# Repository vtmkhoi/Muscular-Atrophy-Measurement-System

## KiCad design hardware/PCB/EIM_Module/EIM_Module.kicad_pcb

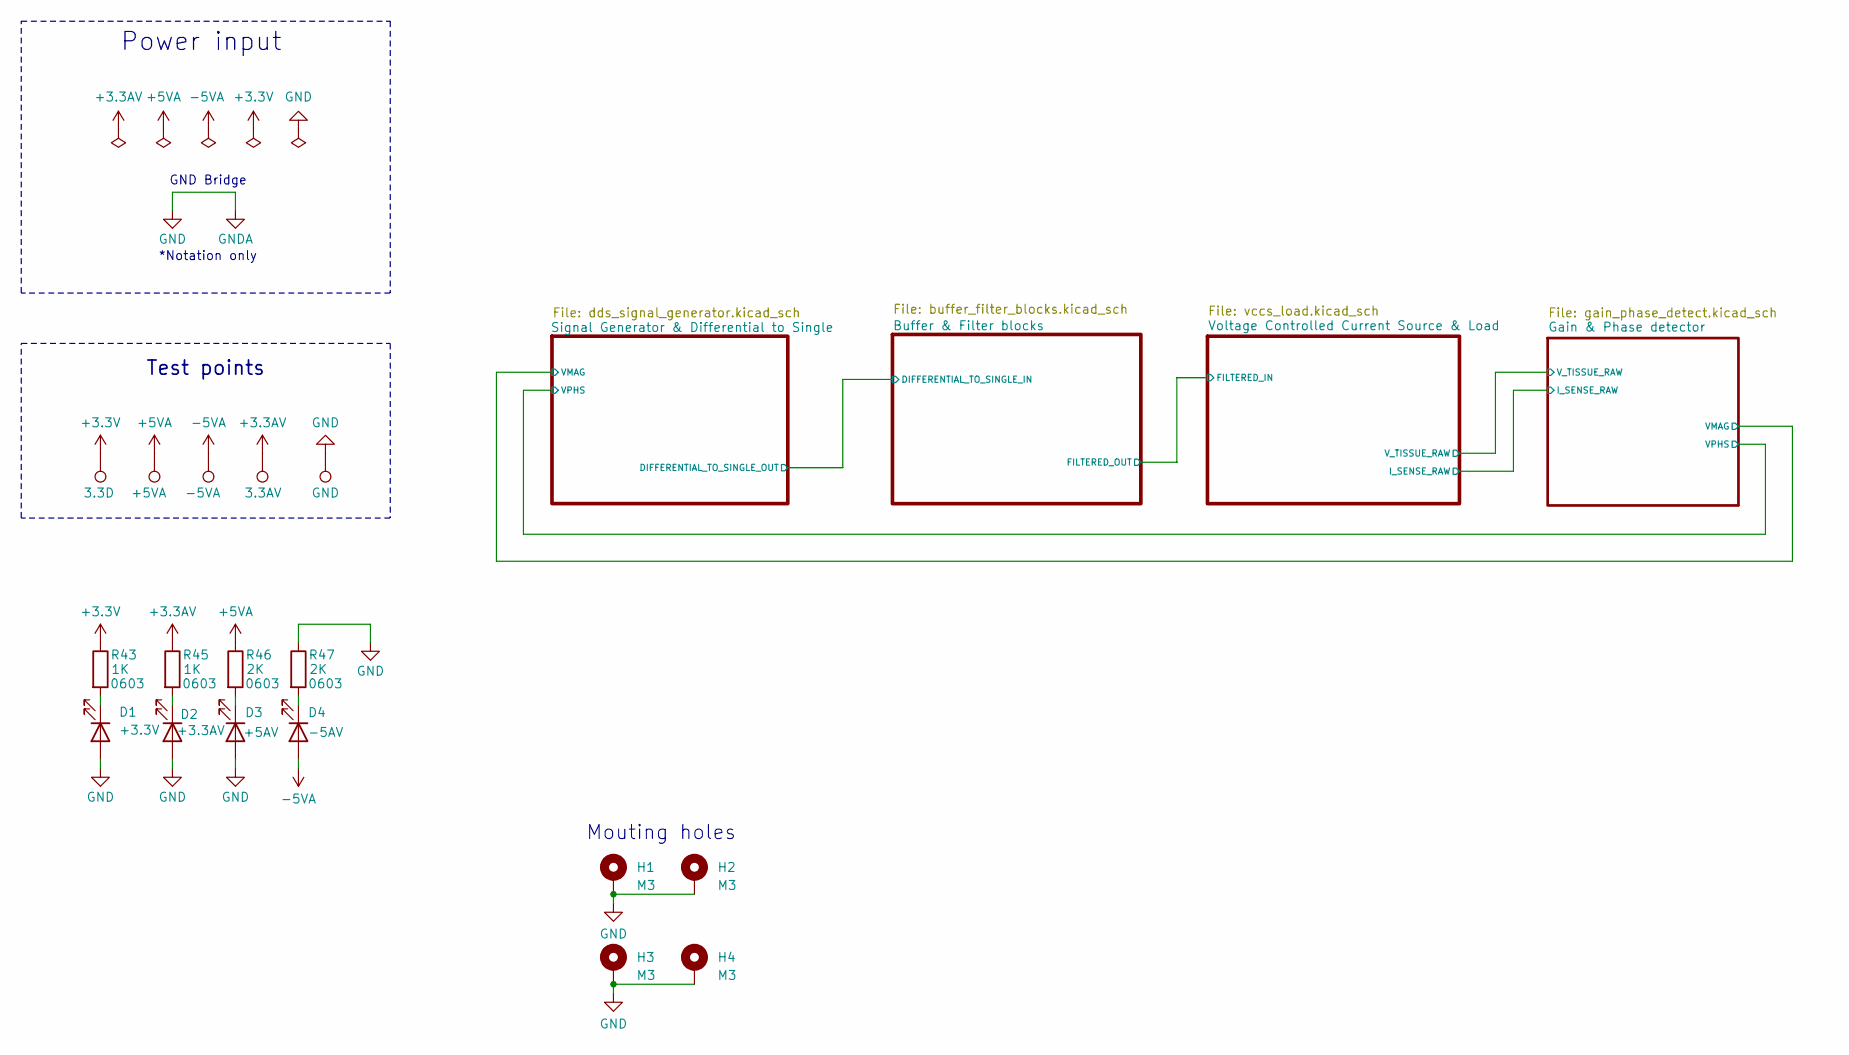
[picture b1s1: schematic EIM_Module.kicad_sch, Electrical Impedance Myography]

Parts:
D1: +3.3V; LED_0603_1608Metric
D2: +3.3AV; LED_0603_1608Metric
D3: +5AV; LED_0603_1608Metric
D4: -5AV; LED_0603_1608Metric
H1, H2, H3, H4: M3; MountingHole_3.2mm_M3_Pad_Via
R43, R45: 1K; R_0603_1608Metric
R46, R47: 2K; R_0603_1608Metric
TP11: 3.3D; TestPoint_Pad_D1.0mm
TP12: +5VA; TestPoint_Pad_D1.0mm
TP13: -5VA; TestPoint_Pad_D1.0mm
TP14: GND; TestPoint_Pad_D1.0mm
TP29: 3.3AV; TestPoint_Pad_D1.0mm

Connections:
+3.3AV: R45.1, TP29.1; also elsewhere on the board
+3.3V: R43.1, TP11.1; also elsewhere on the board
+5VA: R46.1, TP12.1; also elsewhere on the board
-5VA: D4.2 (A), TP13.1; also elsewhere on the board
GND: D1.2 (A), D2.2 (A), D3.2 (A), H1.1, H2.1, H3.1, H4.1, R47.1, TP14.1; also elsewhere on the board
unnamed: D1.1 (K), R43.2
unnamed: D2.1 (K), R45.2
unnamed: D3.1 (K), R46.2
unnamed: D4.1 (K), R47.2

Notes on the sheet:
Power input
GND Bridge
Test points
*Notation only
Mouting holes

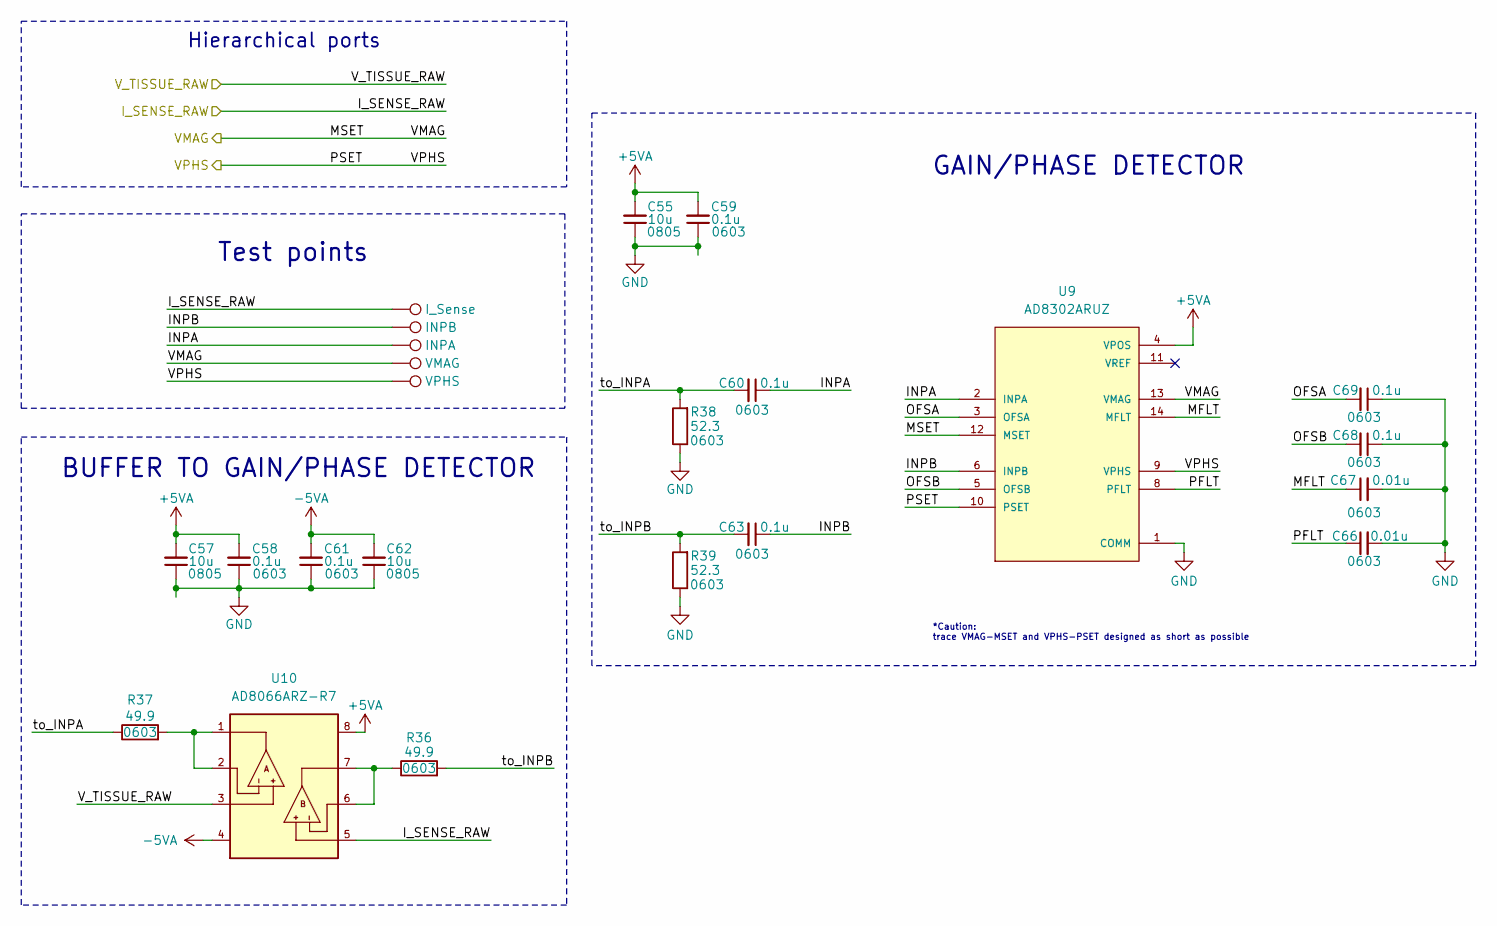
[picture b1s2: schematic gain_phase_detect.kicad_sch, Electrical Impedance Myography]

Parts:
C55, C57, C62: 10u; C_0805_2012Metric
C58, C59, C60, C61, C63, C68, C69: 0.1u; C_0603_1608Metric
C66, C67: 0.01u; C_0603_1608Metric
R36, R37: 49.9; R_0603_1608Metric
R38, R39: 52.3; R_0603_1608Metric
TP21: INPA; TestPoint_Pad_D1.0mm
TP27: I_Sense; TestPoint_Pad_D1.0mm
TP28: INPB; TestPoint_Pad_D1.0mm
TP30: VMAG; TestPoint_Pad_D1.0mm
TP31: VPHS; TestPoint_Pad_D1.0mm
U9: AD8302ARUZ; SOP65P640X120-14N; PARTREV B
U10: AD8066ARZ-R7; SOIC127P600X175-8N

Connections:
+5VA: C55.2, C57.2, C58.2, C59.2, U9.4 (VPOS), U10.8; also elsewhere on the board
-5VA: C61.2, C62.2, U10.4; also elsewhere on the board
/Gain & Phase detector/INPA: C60.1, TP21.1, U9.2 (INPA)
/Gain & Phase detector/INPB: C63.1, TP28.1, U9.6 (INPB)
/Gain & Phase detector/I_SENSE_RAW: TP27.1, U10.5; also elsewhere on the board
/Gain & Phase detector/MFLT: C67.1, U9.14 (MFLT)
/Gain & Phase detector/MSET: TP30.1, U9.12 (MSET), U9.13 (VMAG); also elsewhere on the board
/Gain & Phase detector/OFSA: C69.2, U9.3 (OFSA)
/Gain & Phase detector/OFSB: C68.2, U9.5 (OFSB)
/Gain & Phase detector/PFLT: C66.1, U9.8 (PFLT)
/Gain & Phase detector/PSET: TP31.1, U9.9 (VPHS), U9.10 (PSET); also elsewhere on the board
/Gain & Phase detector/V_TISSUE_RAW: U10.3; also elsewhere on the board
/Gain & Phase detector/to_INPA: C60.2, R37.1, R38.2
/Gain & Phase detector/to_INPB: C63.2, R36.2, R39.2
GND: C55.1, C57.1, C58.1, C59.1, C61.1, C62.1, C66.2, C67.2, C68.1, C69.1, R38.1, R39.1, U9.1 (COMM), U9.7 (COMM); also elsewhere on the board
unnamed: R36.1, U10.6, U10.7
unnamed: R37.2, U10.1, U10.2

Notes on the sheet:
Test points
Hierarchical ports
GAIN/PHASE DETECTOR
BUFFER TO GAIN/PHASE DETECTOR
*Caution: trace VMAG-MSET and VPHS-PSET designed as short as possible

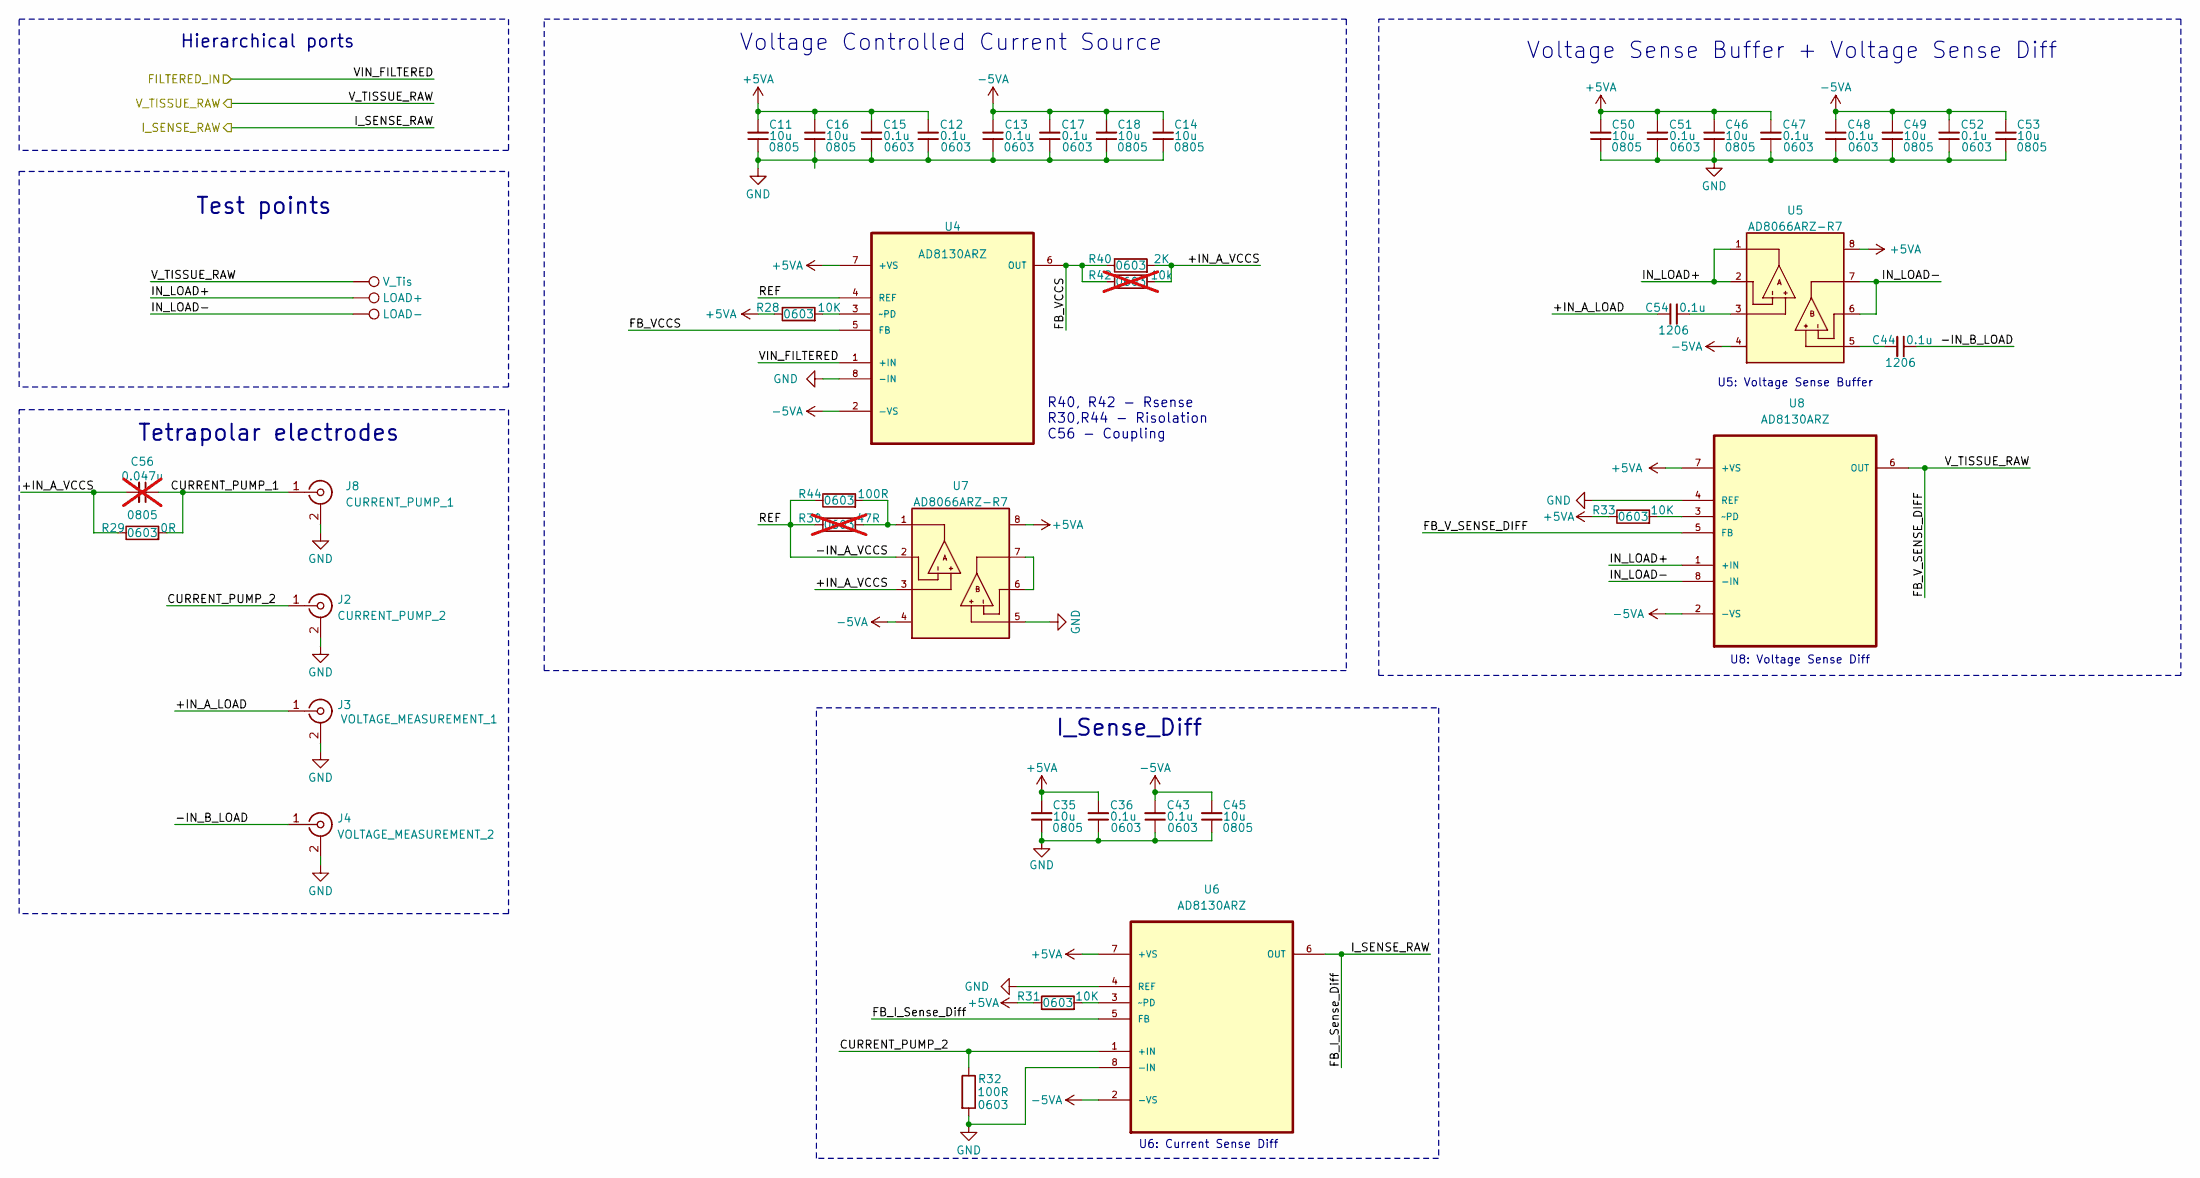
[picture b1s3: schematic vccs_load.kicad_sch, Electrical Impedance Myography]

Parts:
C11, C14, C16, C18, C35, C45, C46, C49, C50, C53: 10u; C_0805_2012Metric
C12, C13, C15, C17, C36, C43, C47, C48, C51, C52: 0.1u; C_0603_1608Metric
C44, C54: 0.1u; C_1206_3216Metric
C56: 0.047u; C_0805_2012Metric; not fitted
J2: CURRENT_PUMP_2; SMA_Molex_73251-2200_Horizontal
J3: VOLTAGE_MEASUREMENT_1; SMA_Molex_73251-2200_Horizontal
J4: VOLTAGE_MEASUREMENT_2; SMA_Molex_73251-2200_Horizontal
J8: CURRENT_PUMP_1; SMA_Molex_73251-2200_Horizontal
R28, R31, R33: 10K; R_0603_1608Metric
R29: 0R; R_0603_1608Metric
R30: 47R; R_0603_1608Metric; not fitted
R32, R44: 100R; R_0603_1608Metric
R40: 2K; R_0603_1608Metric
R42: 10k; R_0603_1608Metric; not fitted
TP17: V_Tis; TestPoint_Pad_D1.0mm
TP19: LOAD+; TestPoint_Pad_D1.0mm
TP20: LOAD-; TestPoint_Pad_D1.0mm
U4, U6, U8: AD8130ARZ; SOIC127P600X175-8N; MPN AD8130ARZ
U5, U7: AD8066ARZ-R7; SOIC127P600X175-8N

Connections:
+5VA: C11.2, C12.2, C15.2, C16.2, C35.2, C36.2, C46.2, C47.2, C50.2, C51.2, R28.1, R31.1, R33.1, U4.7 (+VS), U5.8, U6.7 (+VS), U7.8, U8.7 (+VS); also elsewhere on the board
-5VA: C13.2, C14.2, C17.2, C18.2, C43.2, C45.2, C48.2, C49.2, C52.2, C53.2, U4.2 (-VS), U5.4, U6.2 (-VS), U7.4, U8.2 (-VS); also elsewhere on the board
/Buffer & Filter blocks/VOUT_FILTERED: U4.1 (+IN); also elsewhere on the board
/Gain & Phase detector/I_SENSE_RAW: U6.5 (FB), U6.6 (OUT); also elsewhere on the board
/Gain & Phase detector/V_TISSUE_RAW: TP17.1, U8.5 (FB), U8.6 (OUT); also elsewhere on the board
/Voltage Controlled Current Source & Load/+IN_A_LOAD: C54.2, J3.1 (In)
/Voltage Controlled Current Source & Load/+IN_A_VCCS: C56.2, R29.1, R40.2, R42.2, U7.3
/Voltage Controlled Current Source & Load/-IN_A_VCCS: R30.1, R44.1, U4.4 (REF), U7.2
/Voltage Controlled Current Source & Load/-IN_B_LOAD: C44.1, J4.1 (In)
/Voltage Controlled Current Source & Load/CURRENT_PUMP_1: C56.1, J8.1 (In), R29.2
/Voltage Controlled Current Source & Load/CURRENT_PUMP_2: J2.1 (In), R32.1, U6.1 (+IN)
/Voltage Controlled Current Source & Load/FB_VCCS: R40.1, R42.1, U4.5 (FB), U4.6 (OUT)
/Voltage Controlled Current Source & Load/IN_LOAD+: TP19.1, U5.1, U5.2, U8.1 (+IN)
/Voltage Controlled Current Source & Load/IN_LOAD-: TP20.1, U5.6, U5.7, U8.8 (-IN)
GND: C11.1, C12.1, C13.1, C14.1, C15.1, C16.1, C17.1, C18.1, C35.1, C36.1, C43.1, C45.1, C46.1, C47.1, C48.1, C49.1, C50.1, C51.1, C52.1, C53.1, J2.2 (Ext), J3.2 (Ext), J4.2 (Ext), J8.2 (Ext), R32.2, U4.8 (-IN), U6.4 (REF), U6.8 (-IN), U7.5, U8.4 (REF); also elsewhere on the board
unnamed: C44.2, U5.5
unnamed: C54.1, U5.3
unnamed: R30.2, R44.2, U7.1
unnamed: R28.2, U4.3 (~PD)
unnamed: R31.2, U6.3 (~PD)
unnamed: U7.6, U7.7
unnamed: R33.2, U8.3 (~PD)

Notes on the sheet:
Test points
Voltage Controlled Current Source
R40, R42 - Rsense R30,R44 - Risolation C56 - Coupling
U8: Voltage Sense Diff
Voltage Sense Buffer + Voltage Sense Diff
Tetrapolar electrodes
U5: Voltage Sense Buffer
Hierarchical ports
I_Sense_Diff
U6: Current Sense Diff

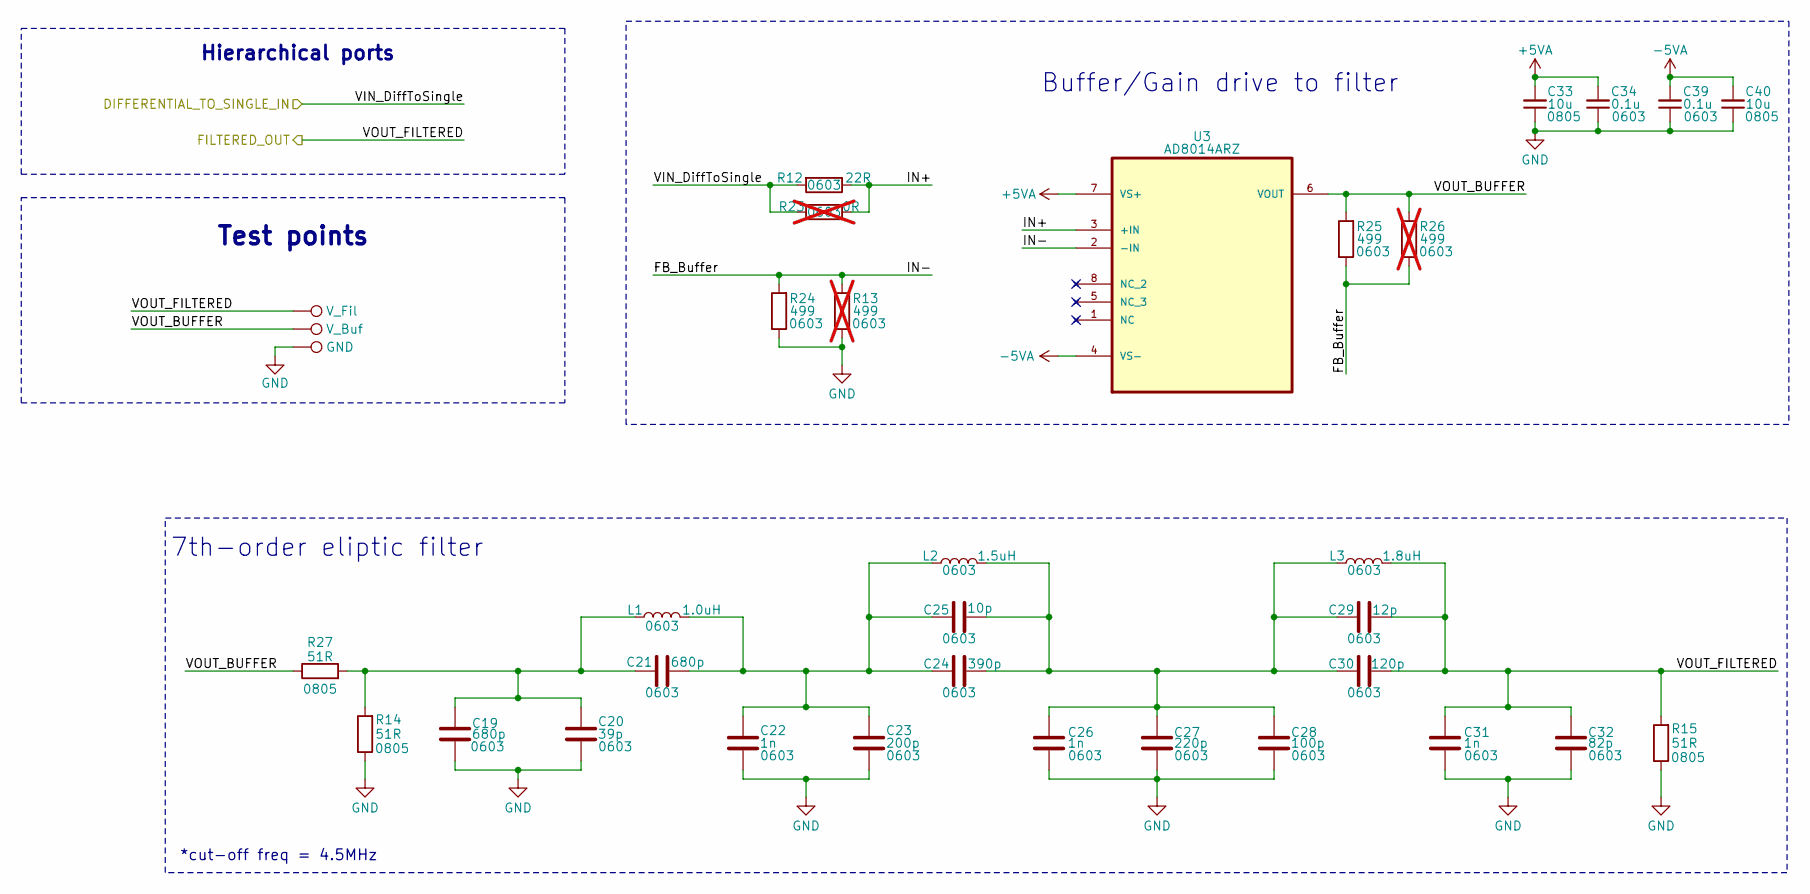
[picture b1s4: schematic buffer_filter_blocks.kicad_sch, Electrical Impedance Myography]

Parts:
C19, C21: 680p; C_0603_1608Metric
C20: 39p; C_0603_1608Metric
C22, C26, C31: 1n; C_0603_1608Metric
C23: 200p; C_0603_1608Metric
C24: 390p; C_0603_1608Metric
C25: 10p; C_0603_1608Metric
C27: 220p; C_0603_1608Metric
C28: 100p; C_0603_1608Metric
C29: 12p; C_0603_1608Metric
C30: 120p; C_0603_1608Metric
C32: 82p; C_0603_1608Metric
C33, C40: 10u; C_0805_2012Metric
C34, C39: 0.1u; C_0603_1608Metric
L1: 1.0uH; L_0603_1608Metric
L2: 1.5uH; L_0603_1608Metric
L3: 1.8uH; L_0603_1608Metric
R12: 22R; R_0603_1608Metric
R13, R26: 499; R_0603_1608Metric; not fitted
R14, R15, R27: 51R; R_0805_2012Metric
R23: 0R; R_0603_1608Metric; not fitted
R24, R25: 499; R_0603_1608Metric
TP22: V_Fil; TestPoint_Pad_D1.0mm
TP23: V_Buf; TestPoint_Pad_D1.0mm
TP25: GND; TestPoint_Pad_D1.0mm
U3: AD8014ARZ; SOIC127P600X175-8N; MPN AD8014ARZ

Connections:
+5VA: C33.2, C34.2, U3.7 (VS+); also elsewhere on the board
-5VA: C39.2, C40.2, U3.4 (VS-); also elsewhere on the board
/Buffer & Filter blocks/FB_Buffer: R13.2, R24.2, R25.1, R26.1, U3.2 (-IN)
/Buffer & Filter blocks/IN+: R12.1, R23.1, U3.3 (+IN)
/Buffer & Filter blocks/VIN_DiffToSingle: R12.2, R23.2; also elsewhere on the board
/Buffer & Filter blocks/VOUT_BUFFER: R25.2, R26.2, R27.1, TP23.1, U3.6 (VOUT)
/Buffer & Filter blocks/VOUT_FILTERED: C29.1, C30.1, C31.2, C32.2, L3.2, R15.2, TP22.1; also elsewhere on the board
GND: C19.1, C20.1, C22.1, C23.1, C26.1, C27.1, C28.1, C31.1, C32.1, C33.1, C34.1, C39.1, C40.1, R13.1, R14.1, R15.1, R24.1, TP25.1; also elsewhere on the board
unnamed: C19.2, C20.2, C21.2, L1.1, R14.2, R27.2
unnamed: C21.1, C22.2, C23.2, C24.2, C25.2, L1.2, L2.1
unnamed: C24.1, C25.1, C26.2, C27.2, C28.2, C29.2, C30.2, L2.2, L3.1

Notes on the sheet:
Hierarchical ports
*cut-off freq = 4.5MHz
7th-order eliptic filter
Test points
Buffer/Gain drive to filter

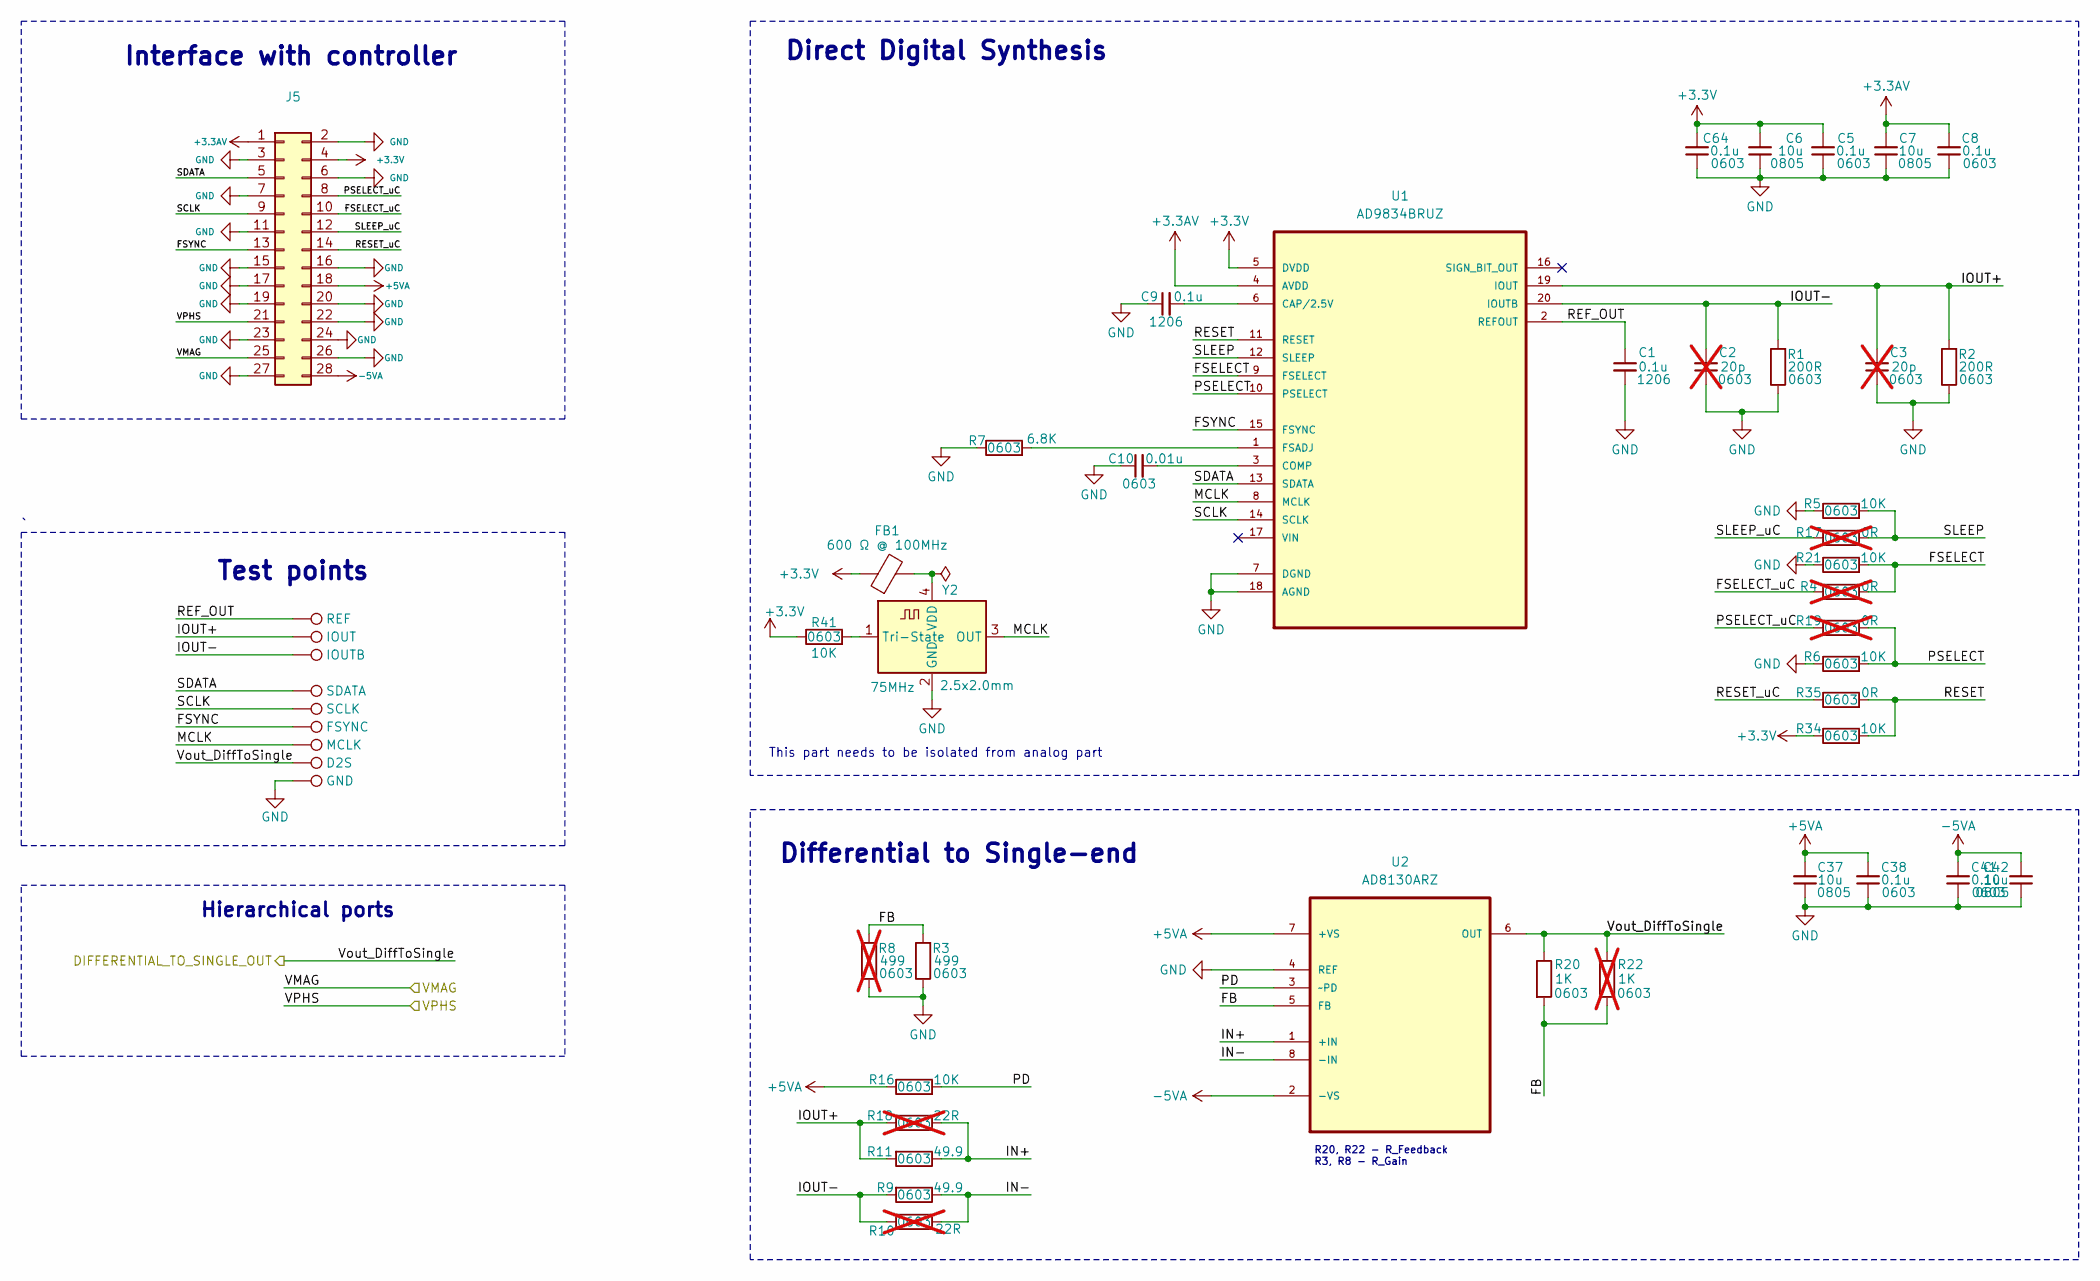
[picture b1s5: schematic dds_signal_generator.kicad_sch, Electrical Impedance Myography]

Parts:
C1, C9: 0.1u; C_1206_3216Metric
C2, C3: 20p; C_0603_1608Metric; not fitted
C5, C8, C38, C41, C64: 0.1u; C_0603_1608Metric
C6, C7, C37, C42: 10u; C_0805_2012Metric
C10: 0.01u; C_0603_1608Metric
FB1: 600 Ω @ 100MHz; L_0603_1608Metric
J5: Interface with controller; PinSocket_2x14_P2.00mm_Vertical
R1, R2: 200R; R_0603_1608Metric
R3: 499; R_0603_1608Metric
R4, R17, R19: 0R; R_0603_1608Metric; not fitted
R5, R6, R16, R21, R34, R41: 10K; R_0603_1608Metric
R7: 6.8K; R_0603_1608Metric
R8: 499; R_0603_1608Metric; not fitted
R9, R11: 49.9; R_0603_1608Metric
R10, R18: 22R; R_0603_1608Metric; not fitted
R20: 1K; R_0603_1608Metric
R22: 1K; R_0603_1608Metric; not fitted
R35: 0R; R_0603_1608Metric
TP1: REF; TestPoint_Pad_D1.0mm
TP2: IOUT; TestPoint_Pad_D1.0mm
TP3: IOUTB; TestPoint_Pad_D1.0mm
TP5: SDATA; TestPoint_Pad_D1.0mm
TP6: SCLK; TestPoint_Pad_D1.0mm
TP7: FSYNC; TestPoint_Pad_D1.0mm
TP8: MCLK; TestPoint_Pad_D1.0mm
TP9: GND; TestPoint_Pad_D1.0mm
TP10: D2S; TestPoint_Pad_D1.0mm
U1: AD9834BRUZ; SOP65P640X120-20N; MPN AD9834BRUZ
U2: AD8130ARZ; SOIC127P600X175-8N; MPN AD8130ARZ
Y2: 75MHz; Oscillator_SMD_SeikoEpson_SG210-4Pin_2.5x2.0mm

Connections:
+3.3AV: C7.2, C8.2, J5.1, U1.4 (AVDD); also elsewhere on the board
+3.3V: C5.2, C6.2, C64.2, FB1.1, J5.4, R34.1, R41.1, U1.5 (DVDD); also elsewhere on the board
+5VA: C37.2, C38.2, J5.18, R16.1, U2.7 (+VS); also elsewhere on the board
-5VA: C41.2, C42.2, J5.28, U2.2 (-VS); also elsewhere on the board
/Buffer & Filter blocks/VIN_DiffToSingle: R20.1, R22.1, TP10.1, U2.6 (OUT); also elsewhere on the board
/Gain & Phase detector/MSET: J5.25; also elsewhere on the board
/Gain & Phase detector/PSET: J5.21; also elsewhere on the board
/Signal Generator & Differential to Single/FB: R3.2, R8.2, R20.2, R22.2, U2.5 (FB)
/Signal Generator & Differential to Single/FSELECT: R4.2, R21.2, U1.9 (FSELECT)
/Signal Generator & Differential to Single/FSELECT_uC: J5.10, R4.1
/Signal Generator & Differential to Single/FSYNC: J5.13, TP7.1, U1.15 (FSYNC)
/Signal Generator & Differential to Single/IN+: R11.1, R18.1, U2.1 (+IN)
/Signal Generator & Differential to Single/IN-: R9.1, R10.1, U2.8 (-IN)
/Signal Generator & Differential to Single/IOUT+: C3.2, R2.2, R11.2, R18.2, TP2.1, U1.19 (IOUT)
/Signal Generator & Differential to Single/IOUT-: C2.2, R1.2, R9.2, R10.2, TP3.1, U1.20 (IOUTB)
/Signal Generator & Differential to Single/MCLK: TP8.1, U1.8 (MCLK), Y2.3 (OUT)
/Signal Generator & Differential to Single/PD: R16.2, U2.3 (~PD)
/Signal Generator & Differential to Single/PSELECT: R6.2, R19.2, U1.10 (PSELECT)
/Signal Generator & Differential to Single/PSELECT_uC: J5.8, R19.1
/Signal Generator & Differential to Single/REF_OUT: C1.1, TP1.1, U1.2 (REFOUT)
/Signal Generator & Differential to Single/RESET: R34.2, R35.2, U1.11 (RESET)
/Signal Generator & Differential to Single/RESET_uC: J5.14, R35.1
/Signal Generator & Differential to Single/SCLK: J5.9, TP6.1, U1.14 (SCLK)
/Signal Generator & Differential to Single/SDATA: J5.5, TP5.1, U1.13 (SDATA)
/Signal Generator & Differential to Single/SLEEP: R5.2, R17.2, U1.12 (SLEEP)
/Signal Generator & Differential to Single/SLEEP_uC: J5.12, R17.1
GND: C1.2, C2.1, C3.1, C5.1, C6.1, C7.1, C8.1, C9.1, C10.1, C37.1, C38.1, C41.1, C42.1, C64.1, J5.2, J5.3, J5.6, J5.7, J5.11, J5.15, J5.16, J5.17, J5.19, J5.20, J5.22, J5.23, J5.24, J5.26, J5.27, R1.1, R2.1, R3.1, R5.1, R6.1, R7.1, R8.1, R21.1, TP9.1, U1.7 (DGND), U1.18 (AGND), U2.4 (REF), Y2.2 (GND); also elsewhere on the board
unnamed: C9.2, U1.6 (CAP/2.5V)
unnamed: C10.2, U1.3 (COMP)
unnamed: R7.2, U1.1 (FSADJ)
unnamed: R41.2, Y2.1 (Tri-State)
unnamed: FB1.2, Y2.4 (VDD)

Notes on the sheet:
This part needs to be isolated from analog part
Interface with controller
Direct Digital Synthesis
Differential to Single-end
R20, R22 - R_Feedback R3, R8 - R_Gain
Test points
Hierarchical ports

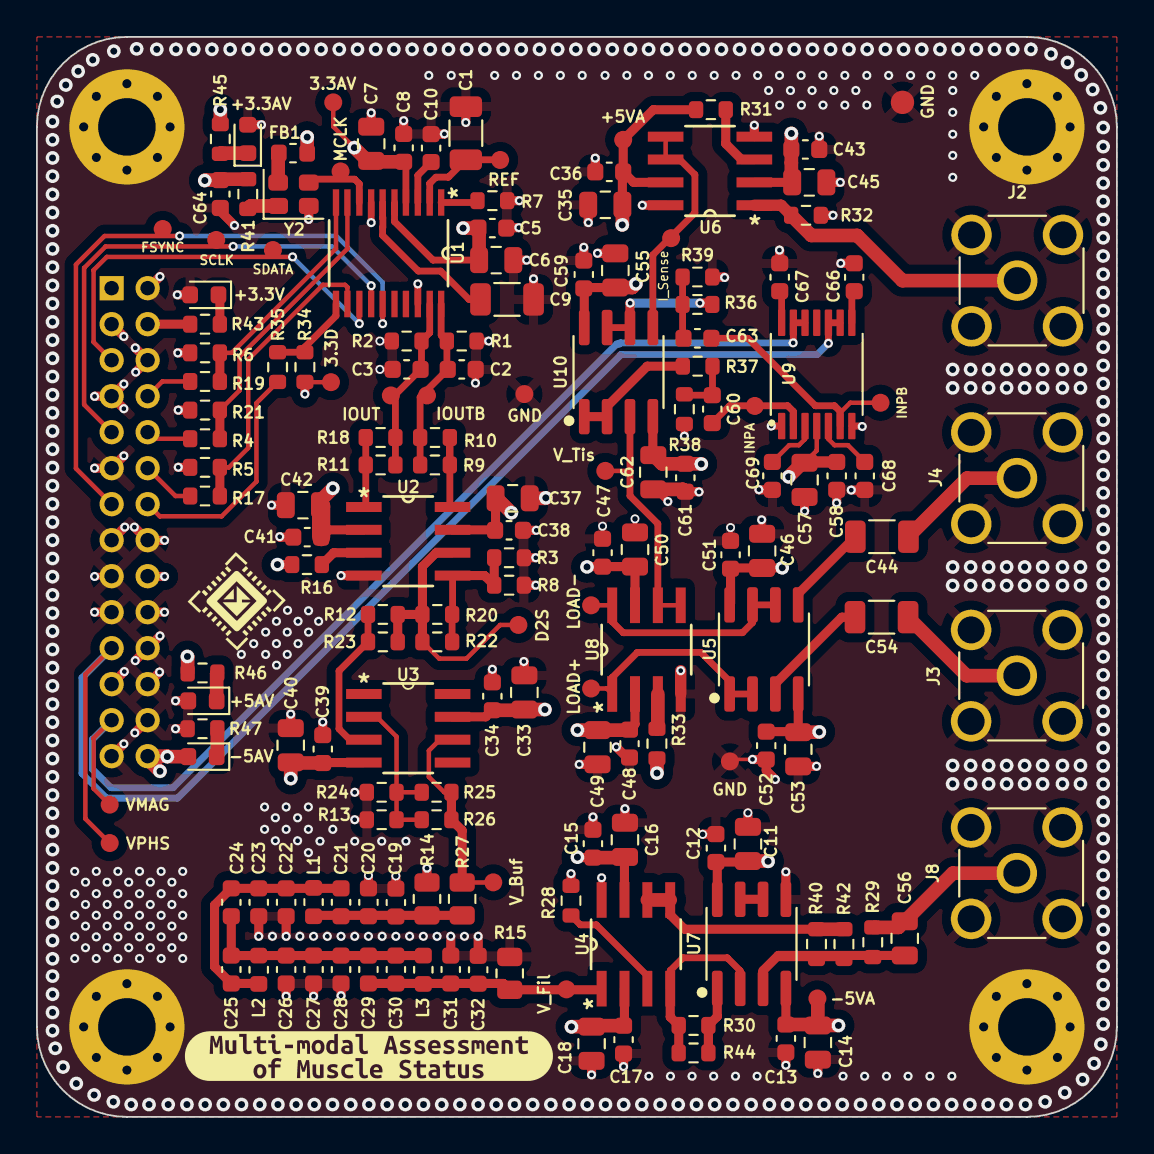
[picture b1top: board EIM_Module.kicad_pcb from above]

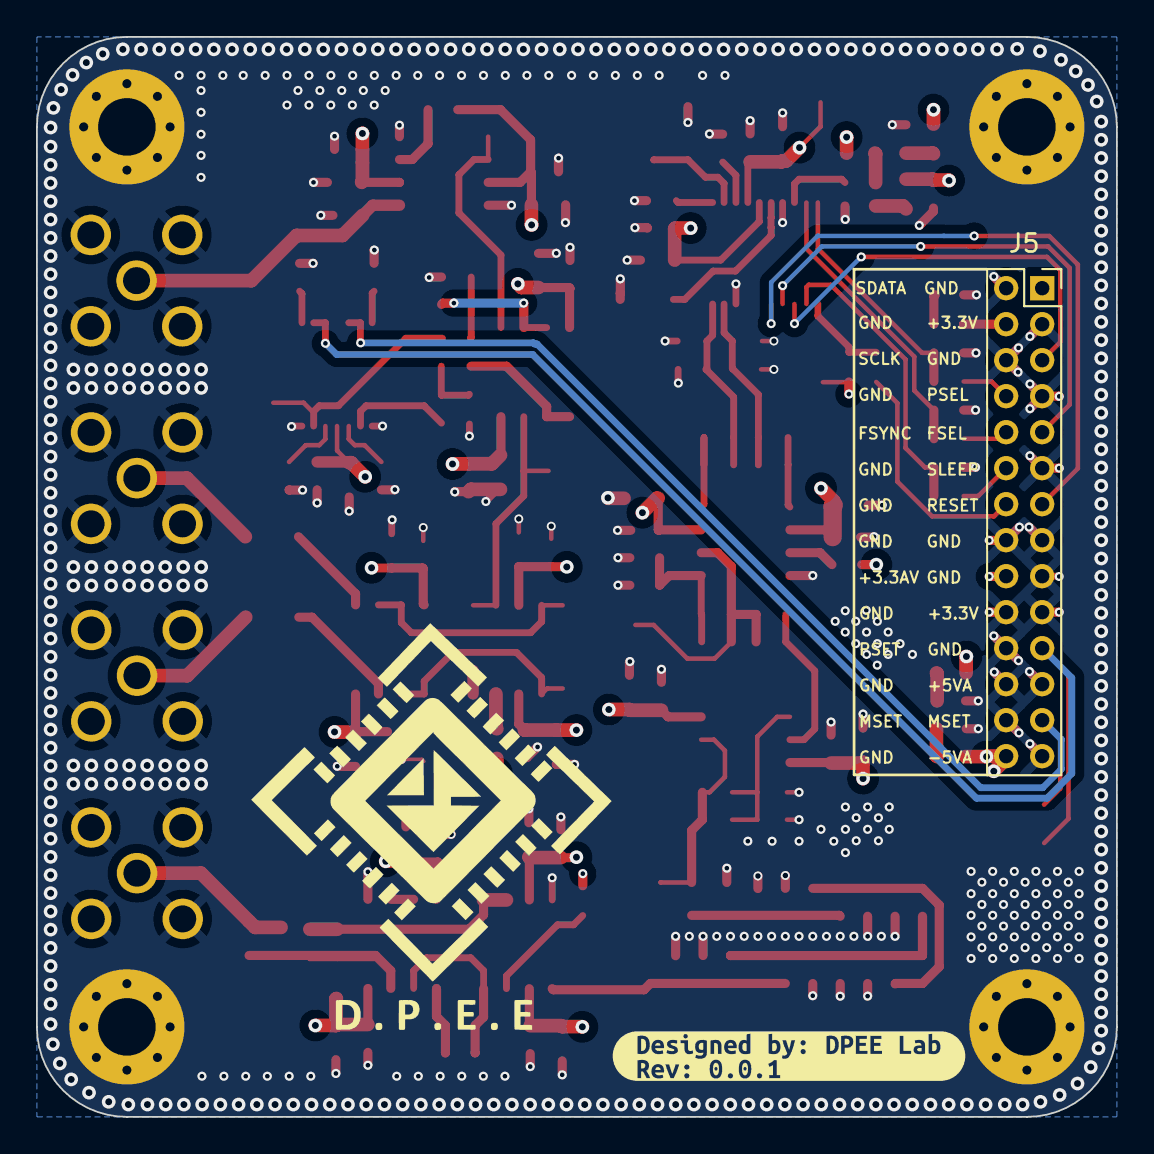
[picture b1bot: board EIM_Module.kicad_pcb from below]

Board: 4 copper layers, 60.0 x 60.0 mm, 169 parts (2 on the bottom side), 71 nets.

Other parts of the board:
kibuzzard-6A1C70B6: G***; kibuzzard-6A1C70B6
kibuzzard-6A1C5277: G***; kibuzzard-6A1C5277

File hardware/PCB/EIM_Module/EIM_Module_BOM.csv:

"Reference","Value","Size","Qty","Description","DNP"
"C1,C4,C5,C8,C9,C12,C13,C15,C17,C34,C36,C38,C39,C41,C43,C44,C47,C48,C51,C52,C54,C58,C59,C61,C68,C69,C70","0.1u","0603,1206","27","Unpolarized capacitor, small symbol",""
"C2,C33","20p","0603","2","Unpolarized capacitor, small symbol","DNP"
"C3,C6,C7,C11,C14,C16,C18,C35,C37,C40,C42,C45,C46,C49,C50,C53,C55,C57,C62","10u","0805","19","Unpolarized capacitor, small symbol",""
"C10,C66,C67","0.01u","0603","3","Unpolarized capacitor, small symbol",""
"C19,C21","680p","0603","2","Unpolarized capacitor",""
"C20","39p","0603","1","Unpolarized capacitor",""
"C22,C26,C31","1n","0603","3","Unpolarized capacitor",""
"C23","200p","0603","1","Unpolarized capacitor",""
"C24","390p","0603","1","Unpolarized capacitor",""
"C25","10p","0603","1","Unpolarized capacitor",""
"C27","220p","0603","1","Unpolarized capacitor",""
"C28","100p","0603","1","Unpolarized capacitor",""
"C29","12p","0603","1","Unpolarized capacitor",""
"C30","120p","0603","1","Unpolarized capacitor",""
"C32","82p","0603","1","Unpolarized capacitor",""
"C56","0.047u","0805","1","Unpolarized capacitor, small symbol","DNP"
"H1,H2,H3,H4","M3","","4","",""
"J1","ADC","","1","Generic connector, single row, 01x02, script generated (kicad-library-utils/schlib/autogen/connector/)",""
"J2","CURRENT_PUMP_2","","1","coaxial connector (BNC, SMA, SMB, SMC, Cinch/RCA, LEMO, ...)",""
"J3","VOLTAGE_MEASUREMENT_1","","1","coaxial connector (BNC, SMA, SMB, SMC, Cinch/RCA, LEMO, ...)",""
"J4","VOLTAGE_MEASUREMENT_2","","1","coaxial connector (BNC, SMA, SMB, SMC, Cinch/RCA, LEMO, ...)",""
"J5","PROG","","1","Generic connector, double row, 02x04, odd/even pin numbering scheme (row 1 odd numbers, row 2 even numbers), script generated (kicad-library-utils/schlib/autogen/connector/)",""
"J6","Dual power supply","","1","Generic connector, single row, 01x03, script generated",""
"J7","Single power supply","","1","Generic connector, single row, 01x02, script generated",""
"J8","CURRENT_PUMP_1","","1","coaxial connector (BNC, SMA, SMB, SMC, Cinch/RCA, LEMO, ...)",""
"L1","1.0uH","0603","1","Inductor",""
"L2","1.5uH","0603","1","Inductor",""
"L3","1.8uH","0603","1","Inductor",""
"R1,R2","200R","0603","2","Resistor",""
"R3,R8,R13,R24,R25,R26","499","0603","6","Resistor","DNP"
"R4,R17,R19,R23,R29,R35","0R","0603","6","Resistor","DNP"
"R5,R6,R16,R21,R28,R31,R33,R34","10K","0603","8","Resistor",""
"R7","6.8K","0603","1","Resistor",""
"R9,R11,R36,R37","49.9","0603","4","Resistor",""
"R10,R12,R18","22R","0603","3","Resistor","DNP"
"R14,R15,R27","51R","0805","3","Resistor",""
"R20,R22","1K","0603","2","Resistor","DNP"
"R30","47R","0603","1","Resistor","DNP"
"R32,R44","100R","0603","2","Resistor",""
"R38,R39","52.3","0603","2","Resistor",""
"R40","2K","0603","1","Resistor",""
"TP1","TP_REFOUT","","1","test point",""
"TP2","TP_IOUT","","1","test point",""
"TP3","TP_IOUTB","","1","test point",""
"TP4","TP_RESET","","1","test point",""
"TP5","TP_SDATA","","1","test point",""
"TP6","TP_SCLK","","1","test point",""
"TP7","TP_FSYNC","","1","test point",""
"TP8","TP_MCLK","","1","test point",""
"TP9,TP19,TP20,TP28,TP30,TP31","TP_GND","","6","test point",""
"TP10","TP_DIF_SIN","","1","test point",""
"TP11","+3.3V_TP","","1","test point",""
"TP12","+5V_TP","","1","test point",""
"TP13","-5V_TP","","1","test point",""
"TP14,TP15","GND_TP","","2","test point",""
"TP16,TP21,TP22","VOUT_FILTERED","","3","test point",""
"TP17,TP23,TP26","VOUT_BUFFER","","3","test point",""
"TP18,TP24,TP27","VIN_DiffToSingle","","3","test point",""
"TP25","GND","","1","test point",""
"U1","AD9834BRUZ","","1","",""
"U2,U4,U6,U8","AD8130ARZ","","4","",""
"U3","AD8014ARZ","","1","",""
"U5,U7,U10","AD8066ARZ-R7","","3","",""
"U9","AD8302ARUZ","","1","",""
"Y2","75MHz","2.5x2.0mm","1","HCMOS Crystal Clock Oscillator, 2.5x2.0 mm SMD",""

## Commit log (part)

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2026-03-08 main/updated category inside BOM
2026-03-08 Create gitignore
2026-03-08 main/initialize submodule folder for project
2026-03-08 Initialize README file for folder hardware
2026-03-08 Rename submodule for EIM
2026-03-18 Updated simulation for EIM and removed PCB for restruct folder
2026-03-18 software/Test board working
2026-03-18 develop/Updated git ignore
2026-03-18 Develop/Updated gitignore
2026-03-23 MAMS-9 Initialize software for AD9833
2026-03-27 MAMS-9 update comment for c file, adding VS Code workspace and pinout configuration file
2026-03-27 MAMS-13 update simulation block for VCCS
2026-03-27 MAMS-10 Update schematic for DDS and Filter, BOM list and meeting docs
2026-03-28 MAMS-10 update meeting note
2026-03-28 develop added git restrict merge main rule
2026-03-28 develop/ update issue creation template
2026-03-28 Update issue templates
2026-03-29 update meeting note template
2026-03-29 Update meeting note templates
2026-03-29 Fixed issue in create template
2026-03-29 Fixed issue template
2026-04-03 MAMS-33 removed MEHCS topology
2026-04-04 MAMS-33 updated VCCS topology and full LOAD block
2026-04-05 MAMS-33 Update schematic for AD9834 and AD8130
2026-04-06 MAMS-33 updated LTSpice simulation due to wrong connection of AD8130 and AD8014
2026-04-06 MAMS-33 updated second order for LOAD and Power block part 1
2026-04-08 MAMS-33 updated schematic for DDS, Diff to Single and Buffer blocks, updated lib for AD8014 used in KiCad
2026-04-08 MAMS-33 updated BOM with new components in EIM
2026-04-09 MAMS-33 updated new bom for filter block
2026-04-09 MAMS-33 updated schematic for filter block
2026-04-12 MAMS-33 Fixed footprint lib for DDS, Buffer, Diff-2-Single and Filter block
2026-04-12 MAMS-33 removed some unused components for BOM
2026-04-12 MAMS-33 updated new value for filter block
2026-04-12 MAMS-33 updated gitignore for ignore large file
2026-04-12 MAMS-33 removed un-used tracked files
2026-04-12 MAMS-33 removed log file and db file in gitignore
2026-04-18 MAMS-33: Updated BOM
2026-04-18 MAMS-33: Update schematic for load block and library
2026-04-19 MAMS-33 updated BOM list
2026-04-19 MAMS-33 changed folder logo footprint
2026-04-19 MAMS-33 updated hyerachical schematic and corrected the load block
2026-05-09 MAMS-33 Updated simulation final and update schematic and PCB
2026-05-09 MAMS-33 Re-structure document folder and update new BOMS either 2nd order list
2026-05-16 MAMS-38 updated PCB layout for EIM with version using connector
2026-05-25 MAMS-40 Updated PCB upto LPF
2026-06-03 MAMS-40 PCB updated for EIM rev 0.0.1
2026-06-06 MAMS-40 PCB for module EIM updated latest
2026-06-06 MAMS-40 Module EIM updated latest
2026-06-07 MAMS-40 Restructed PCB Layout after reviewed
2026-06-07 MAMS-40 Filled power zones
2026-06-14 MAMS-40 updated PCB final version
2026-06-16 MAMS-40 updated PCB EIM latest
2026-06-25 MAMS-43 Minor changes for EIM
